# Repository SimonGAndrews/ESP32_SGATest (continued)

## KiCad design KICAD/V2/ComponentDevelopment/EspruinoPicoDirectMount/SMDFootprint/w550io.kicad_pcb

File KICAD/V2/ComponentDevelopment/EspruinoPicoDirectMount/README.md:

# Espruino Pico Direct-Mount Footprint Work

This directory contains KiCad work for mounting an Espruino Pico directly onto
a daughter board, including the required PCB aperture.

The working footprint is:

```text
SMDFootprint/w550io.pretty/ESPRUINO_PICO_SMD.kicad_mod
```

The directory also contains imported source and experimental project files
used while developing the footprint. They are preserved for review and
provenance; their presence does not make every file a production asset.

Before the Pico daughter-board schematic and PCB are manufactured:

1. Check the pad numbers, dimensions and aperture against the physical Pico
   and authoritative mechanical information.
2. Confirm paste, solder-mask, courtyard and assembly clearances.
3. Copy the accepted footprint into that daughter-board project's local
   footprint library.
4. Record the source and validation in the daughter-board project.

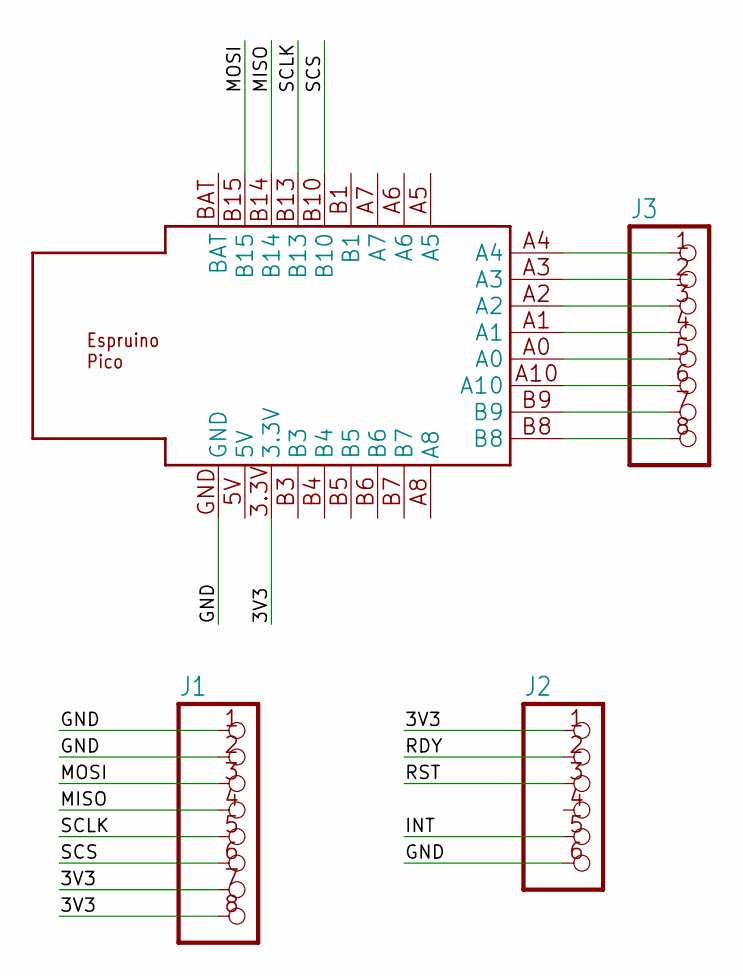
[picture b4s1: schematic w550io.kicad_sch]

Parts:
J1, J3: PINHD-1X8; 1X08
J2: PINHD-1X6; 1X06
U$1: ESPRUINO_PICO_SMD

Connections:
3V3: J1.7, J1.8, J2.1, U$1.3.3V
GND: J1.1, J1.2, J2.6, U$1.GND
INT: J2.5
MISO: J1.4, U$1.B14
MOSI: J1.3, U$1.B15
unnamed: J3.1, U$1.A4
unnamed: J3.2, U$1.A3
unnamed: J3.3, U$1.A2
unnamed: J3.4, U$1.A1
unnamed: J3.5, U$1.A0
unnamed: J3.6, U$1.A10
unnamed: J3.7, U$1.B9
unnamed: J3.8, U$1.B8
RDY: J2.2
RST: J2.3
SCLK: J1.5, U$1.B13
SCS: J1.6, U$1.B10

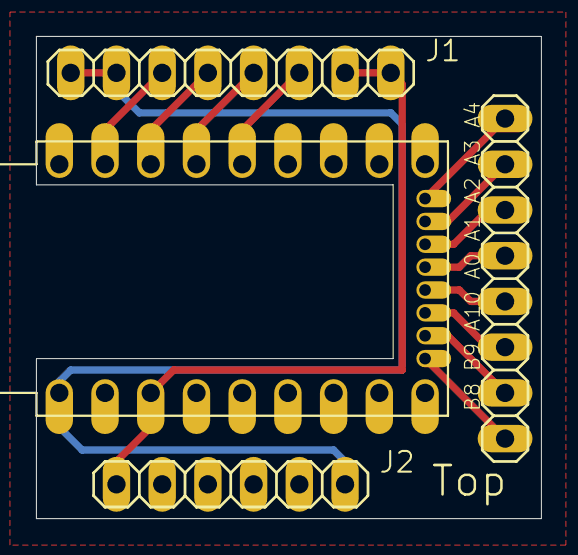
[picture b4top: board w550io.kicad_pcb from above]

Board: 2 copper layers, 28.1 x 26.8 mm, 4 parts (0 on the bottom side), 14 nets.

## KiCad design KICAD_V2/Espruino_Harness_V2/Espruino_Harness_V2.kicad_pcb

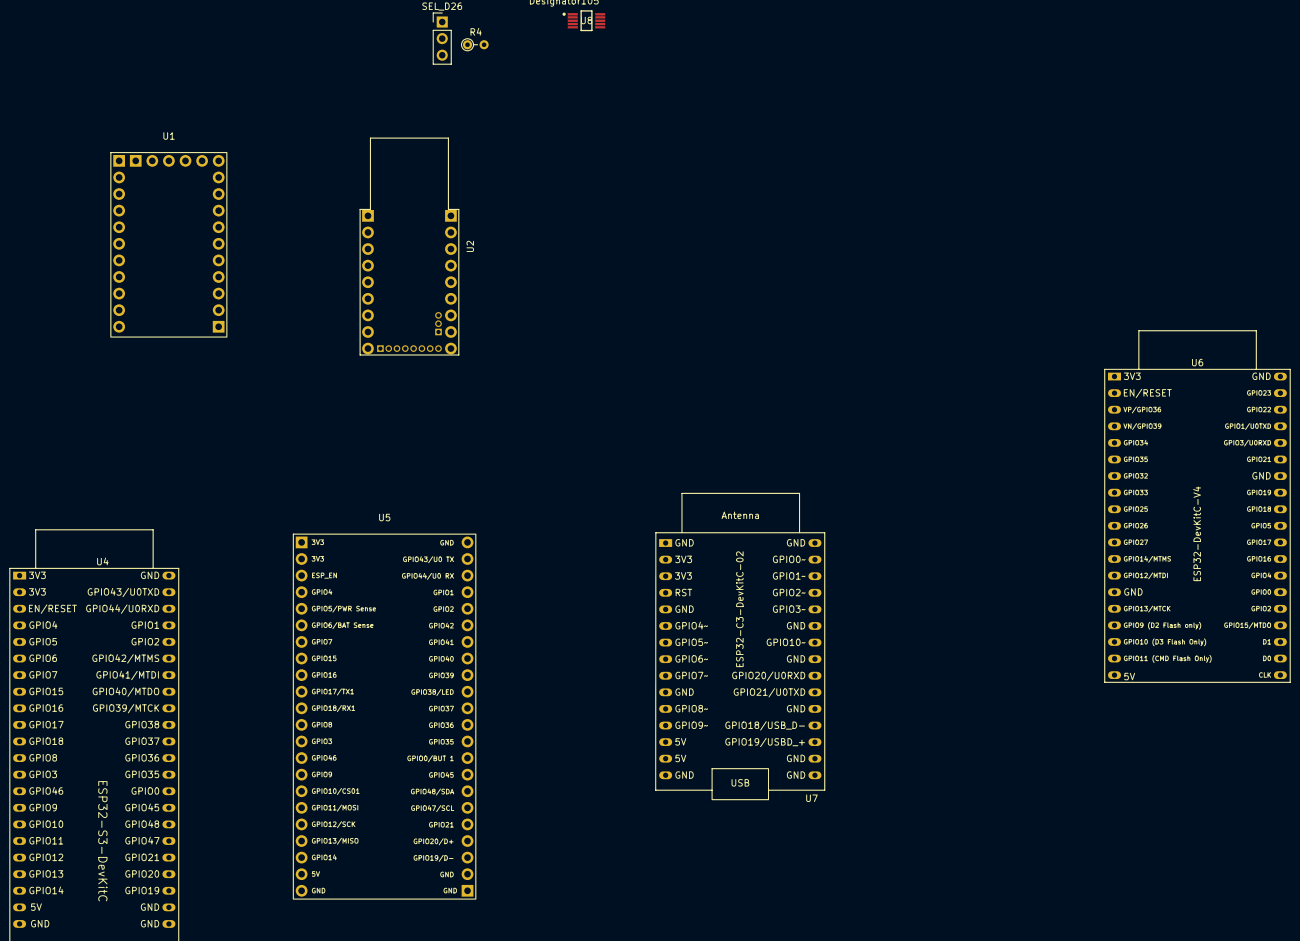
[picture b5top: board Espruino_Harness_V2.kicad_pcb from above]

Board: 2 copper layers, 9 parts (0 on the bottom side), 6 nets, no tracks yet.

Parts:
R4: 470R; R_Axial_DIN0204_L3.6mm_D1.6mm_P2.54mm_Vertical
SEL_D26: LOOP_B / DS2413_PIOB; PinHeader_1x03_P2.54mm_Vertical
U1: Espruino-MDBT42Q-Breakout; Espruino-MDBT42Q-Breakout-Wirewrap
U2: Espruino-Pico-1v4; Espruino-Pico-1v4-Wirewrap
U4: ESP32-S3-DevKitC-1
U5: OLIMEX-ESP32-S3-DevKit-LiPo-EA; OLIMEX-ESP32-S3-DevKit-LiPo-EA-Wirewrap
U6: ESP32-DevKitC-V4; ESP32-DevKitC-V4-Wirewrap
U7: ESP32-C3-DevKitC-02
U8: TMUX1204DGSR; DGS0010A-IPC_B

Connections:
3V3: U7.2 (3V3), U7.3 (3V3)
5V: U7.13 (5V), U7.14 (5V)
/Routing_Control/D26_LOOP_B_IN: R4.2, U8.1 (A0), U8.2 (S1), U8.4 (S3), U8.5 (EN), U8.6 (VDD), U8.7 (S4), U8.9 (S2), U8.10 (A1)
unnamed: R4.1, SEL_D26.2 (C)
unnamed: U6.14 (GND), U6.32 (GND), U6.38 (GND)
unnamed: U7.1 (GND), U7.5 (GND), U7.10 (GND), U7.15 (GND), U7.16 (GND), U7.17 (GND), U7.20 (GND), U7.23 (GND), U7.25 (GND), U7.30 (GND)

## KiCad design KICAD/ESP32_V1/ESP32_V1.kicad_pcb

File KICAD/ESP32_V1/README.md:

# ESP32 DevKitC V4 Espruino Test Harness

Top-level revision: v1.0

The active KiCad 9 project is:

```text
ESP32_V1.kicad_pro
ESP32_V1.kicad_sch
ESP32_V1.pretty/
fp-lib-table
```

`ESP32_V1.sch` and `ESP32_V1.pro` are retained as the original import source.

`ESP32_V1.pretty` is the project-local footprint library. It contains copies
of the proven ESP32-C3 harness footprints needed by this board, plus the
DevKitC V4 1x19 sockets and DS18B20 TO-92 footprint. The DS2413 breakout uses
a 1x04 female socket on the harness PCB and downward-facing male pins on the
removable breakout. Project-local footprints should use the `ESP32_V1:`
footprint-library prefix where available so the project remains portable.

Design notes and the authoritative GPIO table are in:

```text
../../docs/targets/esp32-devkitc-v4/wiring.md
```

The UART test block crosses UART1 and UART2 while UART0 remains available for
the REPL. `SEL_D35` selects D35 between MCP23008 interrupt input and UART1 RX.

## Footprint Policy

| Component group | Footprint approach |
|---|---|
| DevKitC V4 | two `PinSocket_1x19_P2.54mm_Vertical` rows |
| MCP3008 / MCP23008 | DIP-16 / DIP-18 socket footprints |
| DS18B20 | `TO-92_Inline` |
| DS2413 breakout | vertical 1x04, 2.54 mm female pin socket |
| Resistors | vertical 5.08 mm pitch |
| External wiring | 2.54 mm terminal blocks |
| Jumpers/selectors | 2.54 mm pin headers |
| Optional flash | 1x06 pin socket |
| Grove I2C | Seeed Grove 1x04, 2 mm pitch |

Before fixing the PCB placement, verify the centre-to-centre spacing and
orientation of the two 19-pin DevKitC socket rows against the physical DUT.
The PCB silkscreen should then add the complete DevKitC body outline, antenna
end, USB end, and pin-1/orientation marks.

The intended PCB is a wirewrap placement/silkscreen guide. Copper routing is
not required for the first pass; ratsnest/net information remains useful for
checking point-to-point wirewrap connections.

## DS2413 OneWire GPIO Test

`J_DS2413` accepts a removable DS2413 two-channel open-drain GPIO breakout on
the existing `D13_ONEWIRE_DQ` bus:

| `J_DS2413` pin | Signal |
|---:|---|
| 1 | `DS2413_PIOB` |
| 2 | `DS2413_PIOA` |
| 3 | `D13_ONEWIRE_DQ` |
| 4 | GND |

`DS2413_PIOA` and `DS2413_PIOB` each have a 4.7 kÎ© pull-up to 3.3 V. The
breakout is parasite-powered from the OneWire data connection and ground.

`SEL_D33` selects whether `D33` receives the normal `D32` loopback or
`DS2413_PIOA`. `SEL_D26` similarly selects the normal `D25` loopback or
`DS2413_PIOB`. A single 470 Î© resistor in each selector common path protects
the ESP32 input:

```text
D33 <- 470R <- SEL_D33 <- D32 or DS2413_PIOA
D26 <- 470R <- SEL_D26 <- D25 or DS2413_PIOB
```

Fit only one shunt position on each selector. Mark pin 1 and the breakout
orientation clearly on the PCB silkscreen.

## Prototype Board Geometry

`ESP32_V1.kicad_pcb` includes a measured guide for the 90 mm x 70 mm
wirewrap/prototype board used for the first build:

- board outline: 90 mm x 70 mm
- KiCad board outline coordinates: `(70,45)` to `(160,115)`
- main prototype matrix: 31 columns x 26 rows
- matrix pitch: 2.54 mm
- first main matrix hole centre: `(78.5,48.25)`
- last main matrix hole centre: `(154.7,111.75)`
- the main matrix is vertically centred in the 70 mm board height
- four mounting-hole footprints use 1 mm NPTH drills

The first main matrix hole is 8.5 mm from the left board edge. The board also
has vertical side pad columns, visible in the reference photo, but these are
not modelled in the KiCad construction guide because they are not used for the
planned component placement.

The guide circles are locked on `Dwgs.User`. They represent the physical
prototype-board hole pattern for placement/print guidance and are not PCB
drill holes. Keep `Dwgs.User` visible while placing footprints, and include it
only when producing the construction-guide printout.

For footprint placement, set the PCB editor grid to 2.54 mm and place the grid
origin on the first main matrix hole centre, `(78.5,48.25)`. Hole-aligned
placement can then be calculated as:

```text
X = 78.5  + column * 2.54
Y = 48.25 + row    * 2.54
```

Use 1:1 / actual-size print settings for construction guides. A trial print
showed approximately 91 mm for the nominal 90 mm board width when the print
path scaled the output, which is enough to create about 1 mm cumulative drift
towards the lower-right corner.

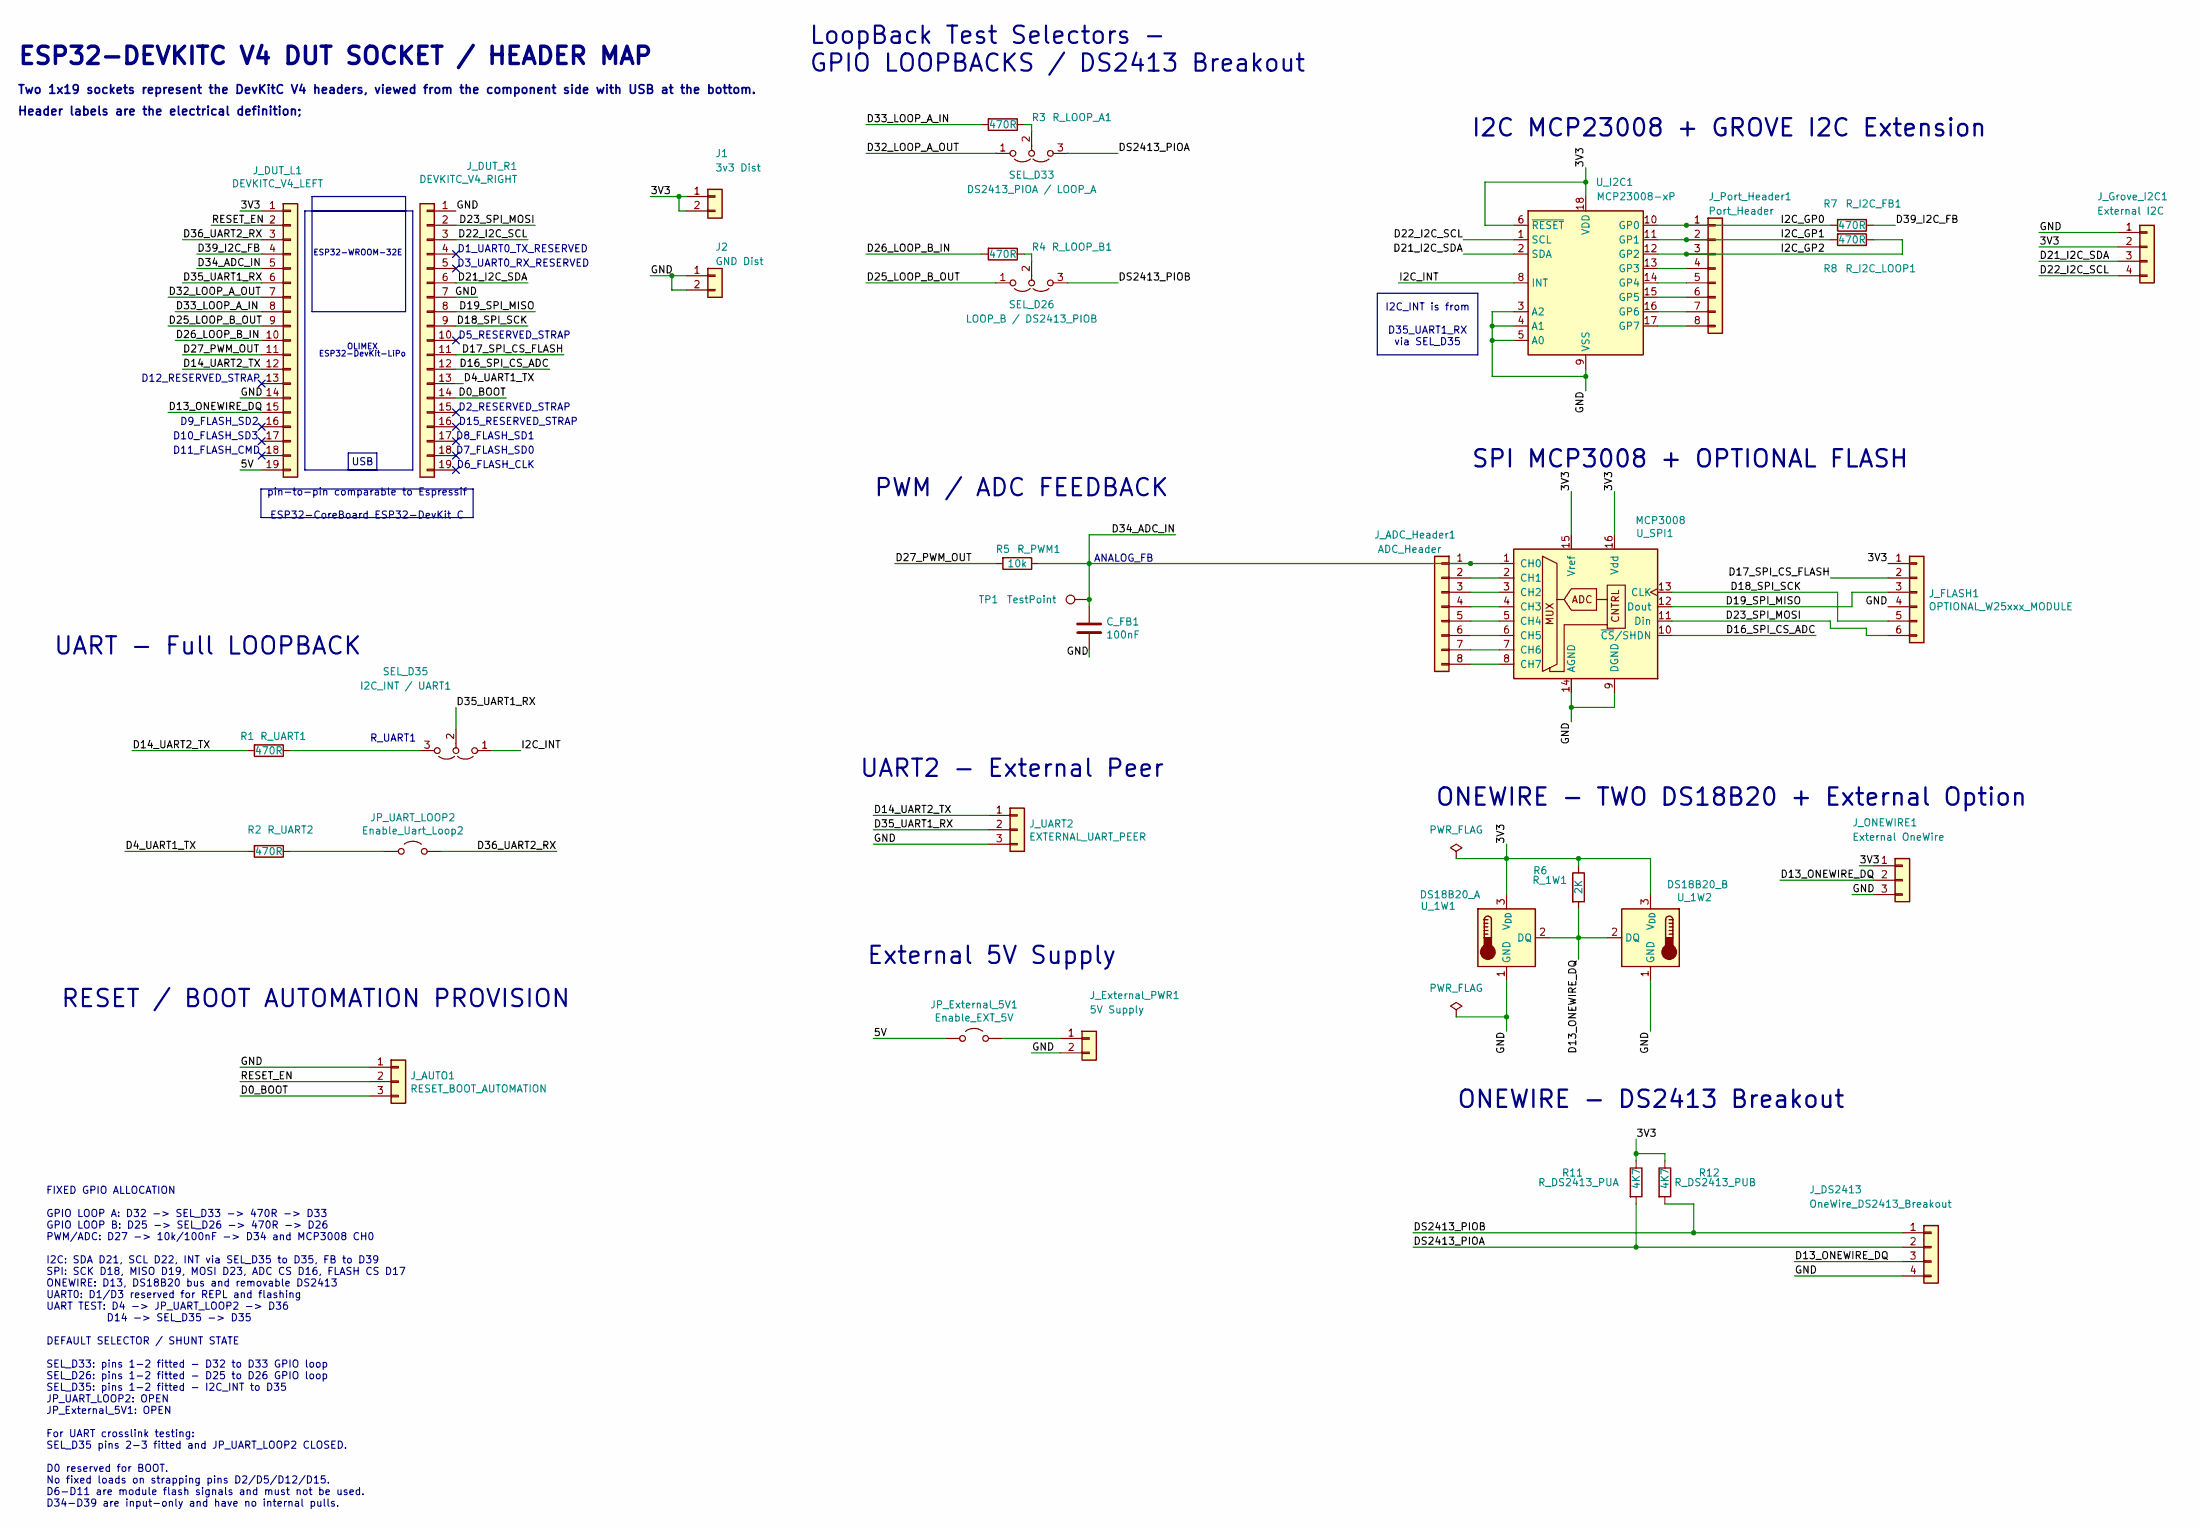
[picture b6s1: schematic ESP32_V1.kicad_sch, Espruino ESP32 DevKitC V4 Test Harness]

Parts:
C_FB1: 100nF; C_Disc_D4.7mm_W2.5mm_P5.00mm
J1: 3v3 Dist; PinHeader_1x02_P2.54mm_Vertical
J2: GND Dist; PinHeader_1x02_P2.54mm_Vertical
JP_External_5V1: Enable_EXT_5V; PinHeader_1x02_P2.54mm_Vertical
JP_UART_LOOP2: Enable_Uart_Loop2; PinHeader_1x02_P2.54mm_Vertical
J_ADC_Header1: ADC_Header; PinHeader_1x08_P2.54mm_Vertical
J_AUTO1: RESET_BOOT_AUTOMATION; TerminalBlock_Phoenix_MPT-0,5-3-2.54_1x03_P2.54mm_Horizontal
J_DS2413: OneWire_DS2413_Breakout; PinSocket_1x04_P2.54mm_Vertical
J_DUT_L1: DEVKITC_V4_LEFT; PinSocket_1x19_P2.54mm_Vertical
J_DUT_R1: DEVKITC_V4_RIGHT; PinSocket_1x19_P2.54mm_Vertical
J_External_PWR1: 5V Supply; TerminalBlock_Phoenix_MPT-0,5-2-2.54_1x02_P2.54mm_Horizontal
J_FLASH1: OPTIONAL_W25xxx_MODULE; PinSocket_1x06_P2.54mm_Vertical
J_Grove_I2C1: External I2C; Grove_1x04_P2mm(SEEED_110990030)
J_ONEWIRE1: External OneWire; TerminalBlock_Phoenix_MPT-0,5-3-2.54_1x03_P2.54mm_Horizontal
J_Port_Header1: Port_Header; PinHeader_1x08_P2.54mm_Vertical
J_UART2: EXTERNAL_UART_PEER; TerminalBlock_Phoenix_MPT-0,5-3-2.54_1x03_P2.54mm_Horizontal
R1, R2, R3, R4, R7, R8: 470R; R_Axial_DIN0204_L3.6mm_D1.6mm_P2.54mm_Vertical
R5: 10k; R_Axial_DIN0204_L3.6mm_D1.6mm_P2.54mm_Vertical
R6: 2K; R_Axial_DIN0204_L3.6mm_D1.6mm_P2.54mm_Vertical
R11, R12: 4K7; R_Axial_DIN0204_L3.6mm_D1.6mm_P2.54mm_Vertical
SEL_D26: LOOP_B / DS2413_PIOB; PinHeader_1x03_P2.54mm_Vertical
SEL_D33: DS2413_PIOA / LOOP_A; PinHeader_1x03_P2.54mm_Vertical
SEL_D35: I2C_INT / UART1; PinHeader_1x03_P2.54mm_Vertical
TP1: TestPoint; TestPoint_THTPad_D1.5mm_Drill0.7mm
U_1W1: DS18B20_A; TO-92_Inline
U_1W2: DS18B20_B; TO-92_Inline
U_I2C1: MCP23008-xP; DIP-18_W7.62mm_Socket
U_SPI1: MCP3008; DIP-16_W7.62mm_Socket

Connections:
/3V3: J1.1, J1.2, J_DUT_L1.1, J_FLASH1.1, J_Grove_I2C1.2, J_ONEWIRE1.1, R6.1, R11.1, R12.1, U_1W1.3 (V_{DD}), U_1W2.3 (V_{DD}), U_I2C1.6 (~RESET), U_I2C1.18 (VDD), U_SPI1.15 (Vref), U_SPI1.16 (Vdd)
/5V: JP_External_5V1.1 (A), J_DUT_L1.19
/D0_BOOT: J_AUTO1.3, J_DUT_R1.14
/D4_UART1_TX: J_DUT_R1.13, R2.2
/D13_ONEWIRE_DQ: J_DS2413.3, J_DUT_L1.15, J_ONEWIRE1.2, R6.2, U_1W1.2 (DQ), U_1W2.2 (DQ)
/D14_UART2_TX: J_DUT_L1.12, J_UART2.1, R1.2
/D16_SPI_CS_ADC: J_DUT_R1.12, U_SPI1.10 (~CS/SHDN)
/D17_SPI_CS_FLASH: J_DUT_R1.11, J_FLASH1.2
/D18_SPI_SCK: J_DUT_R1.9, J_FLASH1.5, U_SPI1.13 (CLK)
/D19_SPI_MISO: J_DUT_R1.8, J_FLASH1.3, U_SPI1.12 (Dout)
/D21_I2C_SDA: J_DUT_R1.6, J_Grove_I2C1.3, U_I2C1.2 (SDA)
/D22_I2C_SCL: J_DUT_R1.3, J_Grove_I2C1.4, U_I2C1.1 (SCL)
/D23_SPI_MOSI: J_DUT_R1.2, J_FLASH1.6, U_SPI1.11 (Din)
/D25_LOOP_B_OUT: J_DUT_L1.9, SEL_D26.1 (A)
/D26_LOOP_B_IN: J_DUT_L1.10, R4.2
/D27_PWM_OUT: J_DUT_L1.11, R5.2
/D32_LOOP_A_OUT: J_DUT_L1.7, SEL_D33.1 (A)
/D33_LOOP_A_IN: J_DUT_L1.8, R3.2
/D34_ADC_IN: C_FB1.1, J_ADC_Header1.1, J_DUT_L1.5, R5.1, TP1.1, U_SPI1.1 (CH0)
/D35_UART1_RX: J_DUT_L1.6, J_UART2.2, SEL_D35.2 (C)
/D36_UART2_RX: JP_UART_LOOP2.2 (B), J_DUT_L1.3
/D39_I2C_FB: J_DUT_L1.4, R7.1
/DS2413_PIOA: J_DS2413.2, R11.2, SEL_D33.3 (B)
/DS2413_PIOB: J_DS2413.1, R12.2, SEL_D26.3 (B)
/GND: C_FB1.2, J2.1, J2.2, J_AUTO1.1, J_DS2413.4, J_DUT_L1.14, J_DUT_R1.1, J_DUT_R1.7, J_External_PWR1.2, J_FLASH1.4, J_Grove_I2C1.1, J_ONEWIRE1.3, J_UART2.3, U_1W1.1 (GND), U_1W2.1 (GND), U_I2C1.3 (A2), U_I2C1.4 (A1), U_I2C1.5 (A0), U_I2C1.9 (VSS), U_SPI1.9 (DGND), U_SPI1.14 (AGND)
/I2C_GP0: J_Port_Header1.1, R7.2, U_I2C1.10 (GP0)
/I2C_GP1: J_Port_Header1.2, R8.2, U_I2C1.11 (GP1)
/I2C_GP2: J_Port_Header1.3, R8.1, U_I2C1.12 (GP2)
/I2C_INT: SEL_D35.1 (A), U_I2C1.8 (INT)
/RESET_EN: J_AUTO1.2, J_DUT_L1.2
unnamed: JP_External_5V1.2 (B), J_External_PWR1.1
unnamed: JP_UART_LOOP2.1 (A), R2.1
unnamed: J_ADC_Header1.2, U_SPI1.2 (CH1)
unnamed: J_ADC_Header1.3, U_SPI1.3 (CH2)
unnamed: J_ADC_Header1.4, U_SPI1.4 (CH3)
unnamed: J_ADC_Header1.5, U_SPI1.5 (CH4)
unnamed: J_ADC_Header1.6, U_SPI1.6 (CH5)
unnamed: J_ADC_Header1.7, U_SPI1.7 (CH6)
unnamed: J_ADC_Header1.8, U_SPI1.8 (CH7)
unnamed: J_Port_Header1.4, U_I2C1.13 (GP3)
unnamed: J_Port_Header1.5, U_I2C1.14 (GP4)
unnamed: J_Port_Header1.6, U_I2C1.15 (GP5)
unnamed: J_Port_Header1.7, U_I2C1.16 (GP6)
unnamed: J_Port_Header1.8, U_I2C1.17 (GP7)
unnamed: R4.1, SEL_D26.2 (C)
unnamed: R3.1, SEL_D33.2 (C)
unnamed: R1.1, SEL_D35.3 (B)

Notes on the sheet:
R_UART1
D12_RESERVED_STRAP
D5_RESERVED_STRAP
ONEWIRE - TWO DS18B20 + External Option
ESP32-DevKit-LiPo
D11_FLASH_CMD
ANALOG_FB
D1_UART0_TX_RESERVED
FIXED GPIO ALLOCATION GPIO LOOP A: D32 -> SEL_D33 -> 470R -> D33 GPIO LOOP B: D25 -> SEL_D26 -> 470R -> D26 PWM/ADC: D27 -> 10k/100nF -> D34 and MCP3008 CH0 I2C: SDA D21, SCL D22, INT via SEL_D35 to D35, FB to D39 SPI: SCK D18, MISO D19, MOSI D23, ADC CS D16, FLASH CS D17 ONEWIRE: D13, DS18B20 bus 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
D15_RESERVED_STRAP
D2_RESERVED_STRAP
ONEWIRE - DS2413 Breakout
ESP32-DEVKITC V4 DUT SOCKET / HEADER MAP
I2C MCP23008 + GROVE I2C Extension
D7_FLASH_SD0
OLIMEX
LoopBack Test Selectors - GPIO LOOPBACKS / DS2413 Breakout
UART2 - External Peer
D9_FLASH_SD2
Two 1x19 sockets represent the DevKitC V4 headers, viewed from the component side with USB at the bottom.
ESP32-WROOM-32E
SPI MCP3008 + OPTIONAL FLASH
RESET / BOOT AUTOMATION PROVISION
D3_UART0_RX_RESERVED
External 5V Supply
UART - Full LOOPBACK
D10_FLASH_SD3
D8_FLASH_SD1
D6_FLASH_CLK
Header labels are the electrical definition;
PWM / ADC FEEDBACK
pin-to-pin comparable to Espressif ESP32-CoreBoard ESP32-DevKit C
USB
I2C_INT is from D35_UART1_RX via SEL_D35

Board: 2 copper layers, 38 parts (0 on the bottom side), 47 nets, no tracks yet.

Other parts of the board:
MH1, MH2, MH3, MH4: MountingHole_1mm; MountingHole_1mm_NPTH

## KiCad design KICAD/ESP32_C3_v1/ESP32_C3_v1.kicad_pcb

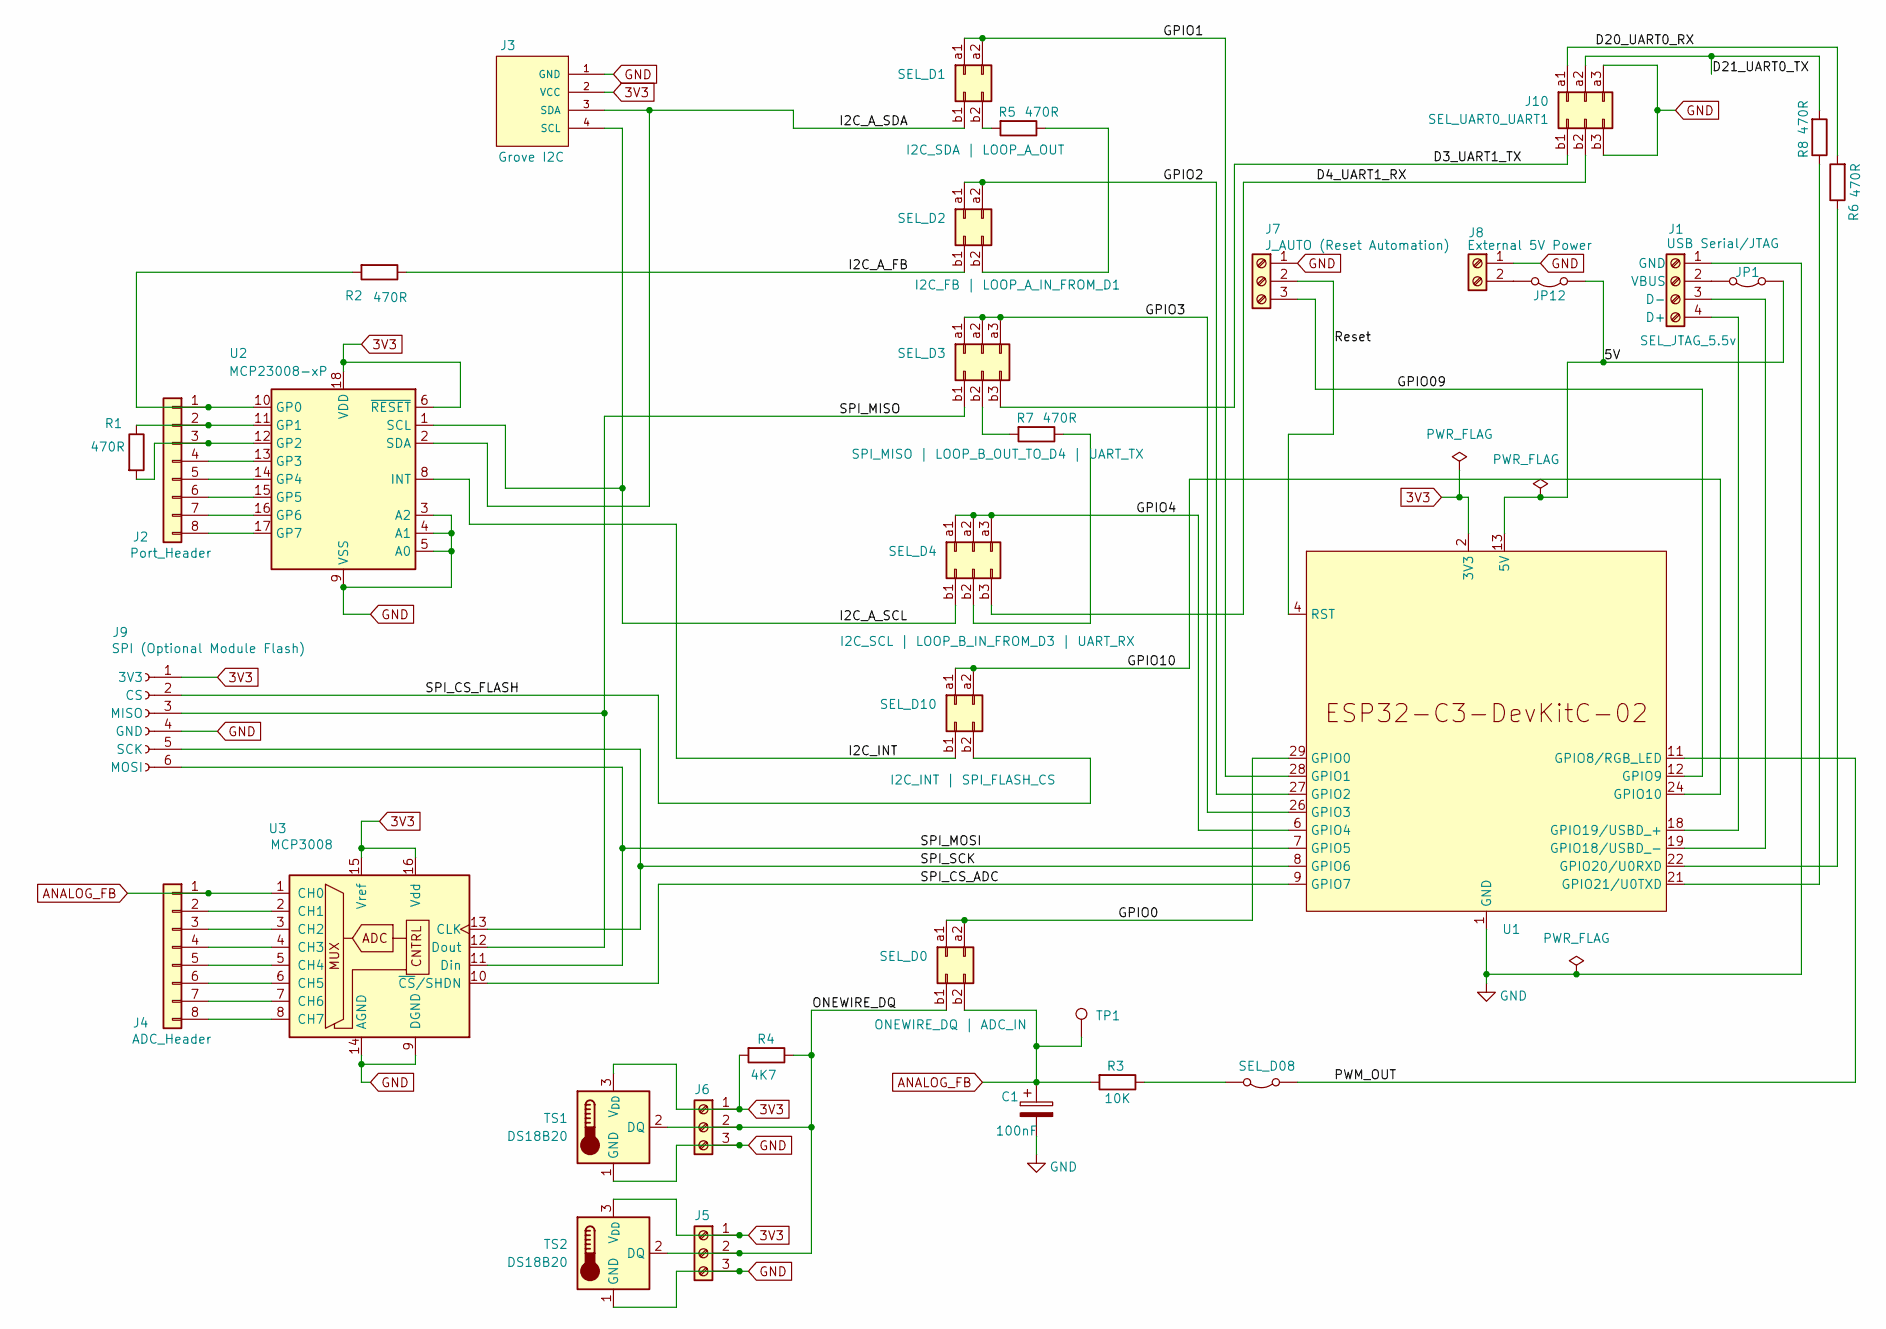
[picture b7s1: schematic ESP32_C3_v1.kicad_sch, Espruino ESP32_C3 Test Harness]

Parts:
C1: 100nF; C_Disc_D4.7mm_W2.5mm_P5.00mm
J1: USB Serial/JTAG; TerminalBlock_Phoenix_MPT-0,5-4-2.54_1x04_P2.54mm_Horizontal
J2: Port_Header; PinHeader_1x08_P2.54mm_Vertical
J3: Grove I2C; Grove_1x04_P2mm(SEEED_110990030)
J4: ADC_Header; PinHeader_1x08_P2.54mm_Vertical
J5, J6: Screw_Terminal_01x03; TerminalBlock_Phoenix_MPT-0,5-3-2.54_1x03_P2.54mm_Horizontal
J7: J_AUTO (Reset Automation); TerminalBlock_Phoenix_MPT-0,5-3-2.54_1x03_P2.54mm_Horizontal
J8: External 5V Power; TerminalBlock_Phoenix_MPT-0,5-2-2.54_1x02_P2.54mm_Horizontal
J9: SPI (Optional Module Flash); PinSocket_1x06_P2.54mm_Vertical
J10: SEL_UART0_UART1; PinHeader_2x03_RowLetter_P2.54mm_Vertical
JP1: SEL_JTAG_5.5v; PinHeader_1x02_P2.54mm_Vertical
JP12: EXT_5V; PinHeader_1x02_P2.54mm_Vertical
R1, R2, R5, R6, R7, R8: 470R; R_Axial_DIN0411_L9.9mm_D3.6mm_P5.08mm_Vertical
R3: 10K; R_Axial_DIN0411_L9.9mm_D3.6mm_P5.08mm_Vertical
R4: 4K7; R_Axial_DIN0411_L9.9mm_D3.6mm_P5.08mm_Vertical
SEL_D0: ONEWIRE_DQ | ADC_IN; PinHeader_2x02_RowLetter_P2.54mm_Vertical
SEL_D1: I2C_SDA | LOOP_A_OUT; PinHeader_2x02_RowLetter_P2.54mm_Vertical
SEL_D2: I2C_FB | LOOP_A_IN_FROM_D1; PinHeader_2x02_RowLetter_P2.54mm_Vertical
SEL_D3: SPI_MISO | LOOP_B_OUT_TO_D4 | UART_TX; PinHeader_2x03_RowLetter_P2.54mm_Vertical
SEL_D4: I2C_SCL | LOOP_B_IN_FROM_D3 | UART_RX; PinHeader_2x03_RowLetter_P2.54mm_Vertical
SEL_D08: PWM_OUT; PinHeader_1x02_P2.54mm_Vertical
SEL_D10: I2C_INT | SPI_FLASH_CS; PinHeader_2x02_RowLetter_P2.54mm_Vertical
TP1: ANALOG_FB; PinHeader_1x01_P2.54mm_Vertical
TS1, TS2: DS18B20; TO-92_Inline
U1: ESP32-C3-DevKitC-02
U2: MCP23008-xP; DIP-18_W7.62mm
U3: MCP3008; DIP-16_W7.62mm

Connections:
3V3: J3.2 (VCC), J5.1, J6.1, J9.1 (3V3), R4.2, TS1.3 (V_{DD}), TS2.3 (V_{DD}), U1.2 (3V3), U1.3 (3V3), U2.6 (~RESET), U2.18 (VDD), U3.15 (Vref), U3.16 (Vdd)
5V: JP1.1 (A), JP12.1 (A), U1.13 (5V), U1.14 (5V)
/D3_UART1_TX: J10.b1, SEL_D3.b3
/D4_UART1_RX: J10.b2, SEL_D4.b3
/D20_UART0_RX: J10.a1, R6.2
/D21_UART0_TX: J10.a2, R8.2
/GPIO0: SEL_D0.a1, SEL_D0.a2, U1.29 (GPIO0)
/GPIO1: SEL_D1.a1, SEL_D1.a2, U1.28 (GPIO1)
/GPIO2: SEL_D2.a1, SEL_D2.a2, U1.27 (GPIO2)
/GPIO3: SEL_D3.a1, SEL_D3.a2, SEL_D3.a3, U1.26 (GPIO3)
/GPIO4: SEL_D4.a1, SEL_D4.a2, SEL_D4.a3, U1.6 (GPIO4)
/GPIO09: J7.3, U1.12 (GPIO9)
/GPIO10: SEL_D10.a1, SEL_D10.a2, U1.24 (GPIO10)
/I2C_A_FB: R2.1, SEL_D2.b1
/I2C_A_SCL: J3.4 (SCL), SEL_D4.b1, U2.1 (SCL)
/I2C_A_SDA: J3.3 (SDA), SEL_D1.b1, U2.2 (SDA)
/I2C_INT: SEL_D10.b1, U2.8 (INT)
/ONEWIRE_DQ: J5.2, J6.2, R4.1, SEL_D0.b1, TS1.2 (DQ), TS2.2 (DQ)
/PWM_OUT: SEL_D08.1 (A), U1.11 (GPIO8/RGB_LED)
/Reset: J7.2, U1.4 (RST)
/SPI_CS_ADC: U1.9 (GPIO7), U3.10 (~CS/SHDN)
/SPI_CS_FLASH: J9.2 (CS), SEL_D10.b2
/SPI_MISO: J9.3 (MISO), SEL_D3.b1, U3.12 (Dout)
/SPI_MOSI: J9.6 (MOSI), U1.7 (GPIO5), U3.11 (Din)
/SPI_SCK: J9.5 (SCK), U1.8 (GPIO6), U3.13 (CLK)
ANALOG_FB: C1.1, J4.1, R3.2, SEL_D0.b2, TP1.1, U3.1 (CH0)
GND: C1.2, J1.1 (GND), J3.1 (GND), J5.3, J6.3, J7.1, J8.1, J9.4 (GND), J10.a3, J10.b3, TS1.1 (GND), TS2.1 (GND), U1.1 (GND), U1.5 (GND), U1.10 (GND), U1.15 (GND), U1.16 (GND), U1.17 (GND), U1.20 (GND), U1.23 (GND), U1.25 (GND), U1.30 (GND), U2.3 (A2), U2.4 (A1), U2.5 (A0), U2.9 (VSS), U3.9 (DGND), U3.14 (AGND)
unnamed: J1.4 (D+), U1.18 (GPIO19/USBD_+)
unnamed: J1.3 (D-), U1.19 (GPIO18/USBD_-)
unnamed: J1.2 (VBUS), JP1.2 (B)
unnamed: J2.1, R2.2, U2.10 (GP0)
unnamed: J2.2, R1.1, U2.11 (GP1)
unnamed: J2.3, R1.2, U2.12 (GP2)
unnamed: J2.4, U2.13 (GP3)
unnamed: J2.5, U2.14 (GP4)
unnamed: J2.6, U2.15 (GP5)
unnamed: J2.7, U2.16 (GP6)
unnamed: J2.8, U2.17 (GP7)
unnamed: J4.2, U3.2 (CH1)
unnamed: J4.3, U3.3 (CH2)
unnamed: J4.4, U3.4 (CH3)
unnamed: J4.5, U3.5 (CH4)
unnamed: J4.6, U3.6 (CH5)
unnamed: J4.7, U3.7 (CH6)
unnamed: J4.8, U3.8 (CH7)
unnamed: J8.2, JP12.2 (B)
unnamed: R5.2, SEL_D1.b2
unnamed: R5.1, SEL_D2.b2
unnamed: R7.2, SEL_D3.b2
unnamed: R7.1, SEL_D4.b2
unnamed: R3.1, SEL_D08.2 (B)
unnamed: R6.1, U1.22 (GPIO20/U0RXD)
unnamed: R8.1, U1.21 (GPIO21/U0TXD)

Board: 2 copper layers, 36 parts (0 on the bottom side), 53 nets, no tracks yet.

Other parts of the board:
MH1, MH2, MH3, MH3#2: MountingHole_1mm; MountingHole_1mm_NPTH

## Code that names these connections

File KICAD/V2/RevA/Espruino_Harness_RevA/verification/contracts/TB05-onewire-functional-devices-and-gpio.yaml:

schema_version: 1
kind: block_contract
block_id: TB05

# Independent machine-checkable intent derived from Standard Test Blocks
# Section 6.5. Sensor-lead length, module orientation, native DNP/hand-fit
# disposition, route sequencing, waveform quality and populated-bus operation
# remain human-reviewed PCB, assembly and functional-test checks.
assertions:
  pin_net:
    # Two removable, externally powered DS18B20 sensor connections.
    - {ref: J501, pin: "1", net: TI_GND}
    - {ref: J501, pin: "2", net: TI_ONEWIRE_DQ}
    - {ref: J501, pin: "3", net: TEST_BLOCK_3V3}
    - {ref: J502, pin: "1", net: TI_GND}
    - {ref: J502, pin: "2", net: TI_ONEWIRE_DQ}
    - {ref: J502, pin: "3", net: TEST_BLOCK_3V3}

    # Removable parasite-powered DS2413 module interface.
    - {ref: J504, pin: "1", net: ONEWIRE_PIOB}
    - {ref: J504, pin: "2", net: ONEWIRE_PIOA}
    - {ref: J504, pin: "3", net: TI_ONEWIRE_DQ}
    - {ref: J504, pin: "4", net: TI_GND}

    # Shared DQ bus, normal/diagnostic resistor-limited pull-up selector and
    # route/observation endpoints.
    - {ref: J503, pin: "1", net: Net-(J503-A)}
    - {ref: R501, pin: "2", net: Net-(J503-A)}
    - {ref: R501, pin: "1", net: TEST_BLOCK_3V3}
    - {ref: J503, pin: "2", net: TI_ONEWIRE_DQ}
    - {ref: J503, pin: "3", net: Net-(J503-B)}
    - {ref: R502, pin: "2", net: Net-(J503-B)}
    - {ref: R502, pin: "1", net: TEST_BLOCK_3V3}
    - {ref: TP501, pin: "1", net: TI_ONEWIRE_DQ}
    - {ref: J901, pin: "14", net: TI_ONEWIRE_DQ}
    - {ref: U601, pin: "6", net: TI_ONEWIRE_DQ}

    # DS2413 PIOA pull-up, protected feedback and observation path.
    - {ref: R504, pin: "1", net: TEST_BLOCK_3V3}
    - {ref: R504, pin: "2", net: ONEWIRE_PIOA}
    - {ref: R505, pin: "1", net: ONEWIRE_PIOA}
    - {ref: TP502, pin: "1", net: ONEWIRE_PIOA}
    - {ref: R505, pin: "2", net: TI_ONEWIRE_GPIO_A_FB}
    - {ref: J901, pin: "15", net: TI_ONEWIRE_GPIO_A_FB}
    - {ref: U602, pin: "11", net: TI_ONEWIRE_GPIO_A_FB}

    # DS2413 PIOB pull-up, protected feedback and observation path.
    - {ref: R503, pin: "1", net: TEST_BLOCK_3V3}
    - {ref: R503, pin: "2", net: ONEWIRE_PIOB}
    - {ref: R506, pin: "1", net: ONEWIRE_PIOB}
    - {ref: TP503, pin: "1", net: ONEWIRE_PIOB}
    - {ref: R506, pin: "2", net: TI_ONEWIRE_GPIO_B_FB}
    - {ref: J901, pin: "17", net: TI_ONEWIRE_GPIO_B_FB}
    - {ref: U605, pin: "8", net: TI_ONEWIRE_GPIO_B_FB}

    # Local supply and ground observation points.
    - {ref: TP504, pin: "1", net: TEST_BLOCK_3V3}
    - {ref: TP505, pin: "1", net: TI_GND}

  component_value:
    - {ref: J501, value: DS18B20_SENSOR_A}
    - {ref: J502, value: DS18B20_SENSOR_B}
    - {ref: J503, value: 2K2_DQ_4K7}
    - {ref: J504, value: DS2413_MODULE}
    - {ref: R501, value: 2.2k}
    - {ref: R502, value: 4.7k}
    - {ref: R503, value: 4.7k}
    - {ref: R504, value: 4.7k}
    - {ref: R505, value: 470R}
    - {ref: R506, value: 470R}
    - {ref: TP501, value: ONEWIRE_DQ}
    - {ref: TP502, value: ONEWIRE_PIOA}
    - {ref: TP503, value: ONEWIRE_PIOB}
    - {ref: TP504, value: 3V3}
    - {ref: TP505, value: GND}

  forbidden_same_net:
    - id: TB05-F01
      endpoints: [J501.1, J501.3]
      reason: Sensor A ground and switched 3.3 V must remain separate.
    - id: TB05-F02
      endpoints: [J502.1, J502.3]
      reason: Sensor B ground and switched 3.3 V must remain separate.
    - id: TB05-F03
      endpoints: [J504.3, J504.4]
      reason: The DS2413 DQ and ground pins must remain separate.
    - id: TB05-F04
      endpoints: [J503.1, J503.2]
      reason: The normal pull-up selector position must retain R501 rather than tie DQ directly high.
    - id: TB05-F05
      endpoints: [J503.2, J503.3]
      reason: The diagnostic pull-up selector position must retain R502 rather than tie DQ directly high.
    - id: TB05-F06
      endpoints: [R501.1, R501.2]
      reason: The normal 2.2 kOhm pull-up resistor must not be bypassed.
    - id: TB05-F07
      endpoints: [R502.1, R502.2]
      reason: The diagnostic 4.7 kOhm pull-up resistor must not be bypassed.
    - id: TB05-F08
      endpoints: [J504.1, J504.3]
      reason: DS2413 PIOB must remain separate from the 1-Wire DQ bus.
    - id: TB05-F09
      endpoints: [J504.2, J504.3]
      reason: DS2413 PIOA must remain separate from the 1-Wire DQ bus.
    - id: TB05-F10
      endpoints: [J504.1, J504.2]
      reason: The two independently controlled DS2413 PIO channels must remain separate.
    - id: TB05-F11
      endpoints: [R505.1, R505.2]
      reason: The PIOA target-feedback path must retain its 470 Ohm protection resistor.
    - id: TB05-F12
      endpoints: [R506.1, R506.2]
      reason: The PIOB target-feedback path must retain its 470 Ohm protection resistor.
    - id: TB05-F13
      endpoints: [U601.6, U602.11]
      reason: DQ and the routed PIOA feedback endpoint must remain independent.
    - id: TB05-F14
      endpoints: [U601.6, U605.8]
      reason: DQ and the routed PIOB feedback endpoint must remain independent.

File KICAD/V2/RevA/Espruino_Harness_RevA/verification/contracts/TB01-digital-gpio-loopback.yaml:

schema_version: 1
kind: block_contract
block_id: TB01

# Independent machine-checkable intent derived from Standard Test Blocks
# Section 6.1 and the accepted V1 functional pattern. V1 proves the circuit
# function, not the Rev-A SMD package, header, shunt or PCB implementation.
# Fitted-shunt state and physical accessibility remain human-reviewed
# assembly and PCB-stage checks rather than schema-version 1 assertions.
assertions:
  pin_net:
    # Pair A: output-side test point, 470 ohm protection, hard-isolation
    # header and input-side test point.
    - {ref: R101, pin: "1", net: TI_GPIO_LOOP_A_OUT}
    - {ref: R101, pin: "2", net: Net-(JP101-A)}
    - {ref: JP101, pin: "1", net: Net-(JP101-A)}
    - {ref: JP101, pin: "2", net: TI_GPIO_LOOP_A_IN}
    - {ref: TP101, pin: "1", net: TI_GPIO_LOOP_A_OUT}
    - {ref: TP102, pin: "1", net: TI_GPIO_LOOP_A_IN}

    # Pair B has the same protected and independently isolated structure.
    - {ref: R102, pin: "1", net: TI_GPIO_LOOP_B_OUT}
    - {ref: R102, pin: "2", net: Net-(JP102-A)}
    - {ref: JP102, pin: "1", net: Net-(JP102-A)}
    - {ref: JP102, pin: "2", net: TI_GPIO_LOOP_B_IN}
    - {ref: TP103, pin: "1", net: TI_GPIO_LOOP_B_OUT}
    - {ref: TP104, pin: "1", net: TI_GPIO_LOOP_B_IN}

  component_value:
    - {ref: R101, value: 470R}
    - {ref: R102, value: 470R}
    - {ref: JP101, value: LOOP_A_ISOLATION}
    - {ref: JP102, value: LOOP_B_ISOLATION}
    - {ref: TP101, value: LOOP_A_OUT}
    - {ref: TP102, value: LOOP_A_IN}
    - {ref: TP103, value: LOOP_B_OUT}
    - {ref: TP104, value: LOOP_B_IN}

  forbidden_same_net:
    # The resistor and removable shunt must remain real series elements; a
    # direct copper bypass would defeat protection or hard isolation.
    - id: TB01-F01
      endpoints: [R101.1, R101.2]
      reason: Pair A must retain its 470 ohm series resistor.
    - id: TB01-F02
      endpoints: [JP101.1, JP101.2]
      reason: Pair A must retain a removable hard-isolation point.
    - id: TB01-F03
      endpoints: [R102.1, R102.2]
      reason: Pair B must retain its 470 ohm series resistor.
    - id: TB01-F04
      endpoints: [JP102.1, JP102.2]
      reason: Pair B must retain a removable hard-isolation point.

    # The two loopback pairs must remain electrically independent.
    - id: TB01-F05
      endpoints: [R101.1, R102.1]
      reason: Loopback A and B outputs must not be joined.
    - id: TB01-F06
      endpoints: [R101.1, JP102.2]
      reason: Loopback A output must not join loopback B input.
    - id: TB01-F07
      endpoints: [JP101.2, R102.1]
      reason: Loopback A input must not join loopback B output.
    - id: TB01-F08
      endpoints: [JP101.2, JP102.2]
      reason: Loopback A and B inputs must not be joined.

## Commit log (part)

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2026-05-17 Initial Readme
2026-05-18 Add ESP32-C3 KiCad harness template
2026-05-18 Add ESP32 test harness wiring specs
2026-05-26 Ignore KiCad generated working files
2026-05-26 Align ESP32-C3 harness docs with schematic
2026-05-26 Add cleaned ESP32-C3 harness KiCad project
2026-05-28 Add ESP32-C3 harness v1 PCB draft
2026-05-28 Add ESP32-C3 PCB wirewrap silkscreen guide
2026-06-04 Add ESP32-C3 schematic v1.1 UART crosslink
2026-06-04 Document ESP32-C3 v1.1 UART crosslink mode
2026-06-04 Refine ESP32-C3 v1.1 PCB layout
2026-06-10 Document ESP32-C3 v1.1 J10 UART connector
2026-06-10 Refine ESP32-C3 v1.1 J10 UART schematic and PCB
2026-06-10 Add agent handoff notes
2026-06-17 feat(test-harness): add ESP32-C3 REPL validation and OneWire soak scripts
2026-06-17 docs(harness): add ESP32-C3 REPL bring-up procedure
2026-06-17 docs(onewire): record investigation, trace analysis, and fix validation
2026-06-17 docs(handoff): add new-thread bootstrap index and current repo heads
2026-06-21 docs/tools: add digitalPulse split-investigation material
2026-06-21 Add ESP32 DevKitC V4 harness schematic
2026-06-21 Document ESP32 DevKitC V4 harness wiring
2026-06-24 Progress ESP32 V1 KiCad PCB design
2026-06-24 Align ESP32 V1 PCB guide grid and placement
2026-06-24 Document ESP32 V1 prototype board geometry
2026-06-25 Restructure harness docs and hardware outputs
2026-06-29 Finalize ESP32_V1 v1.0 build documentation
